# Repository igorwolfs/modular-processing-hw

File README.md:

# MCU-BOARD

## Acoustic-carrier Project
The goal is to design a small CPU board, with some RAM and connectors, that can
- Drive the piezo-driver / inverter board
- Save about 1 second of data from 2 30 MHz ADC's
	- Reflection at origin-piezo
	- Transmission from origin to second-piezo
- Processing of the data on the MCU in the next few seconds
- Storage of the processed data on an SD-CARD
- Transmission of the processed data over Hi-Speed USB / Ethernet to a computer

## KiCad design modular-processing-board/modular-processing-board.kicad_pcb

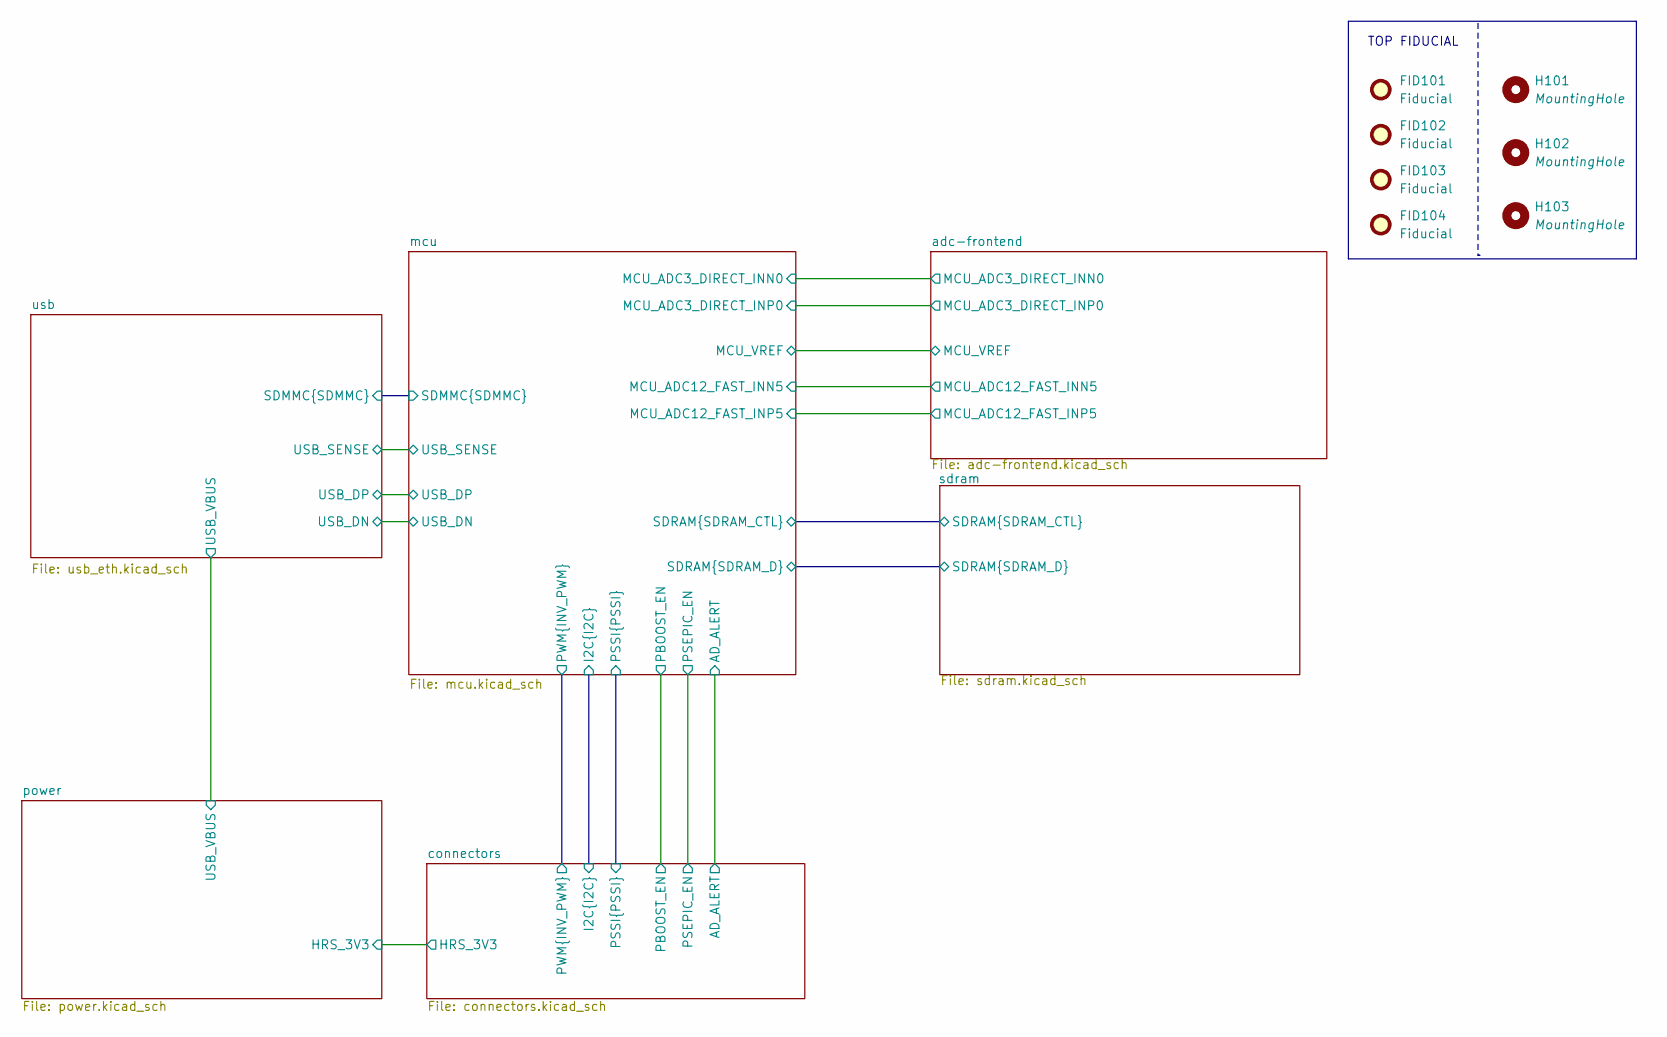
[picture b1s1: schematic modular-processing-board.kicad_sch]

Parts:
FID101, FID102, FID103, FID104: Fiducial; Fiducial_1mm_Mask2mm
H101, H102, H103: MountingHole; ToolingHole_1.152mm

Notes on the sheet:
TOP FIDUCIAL

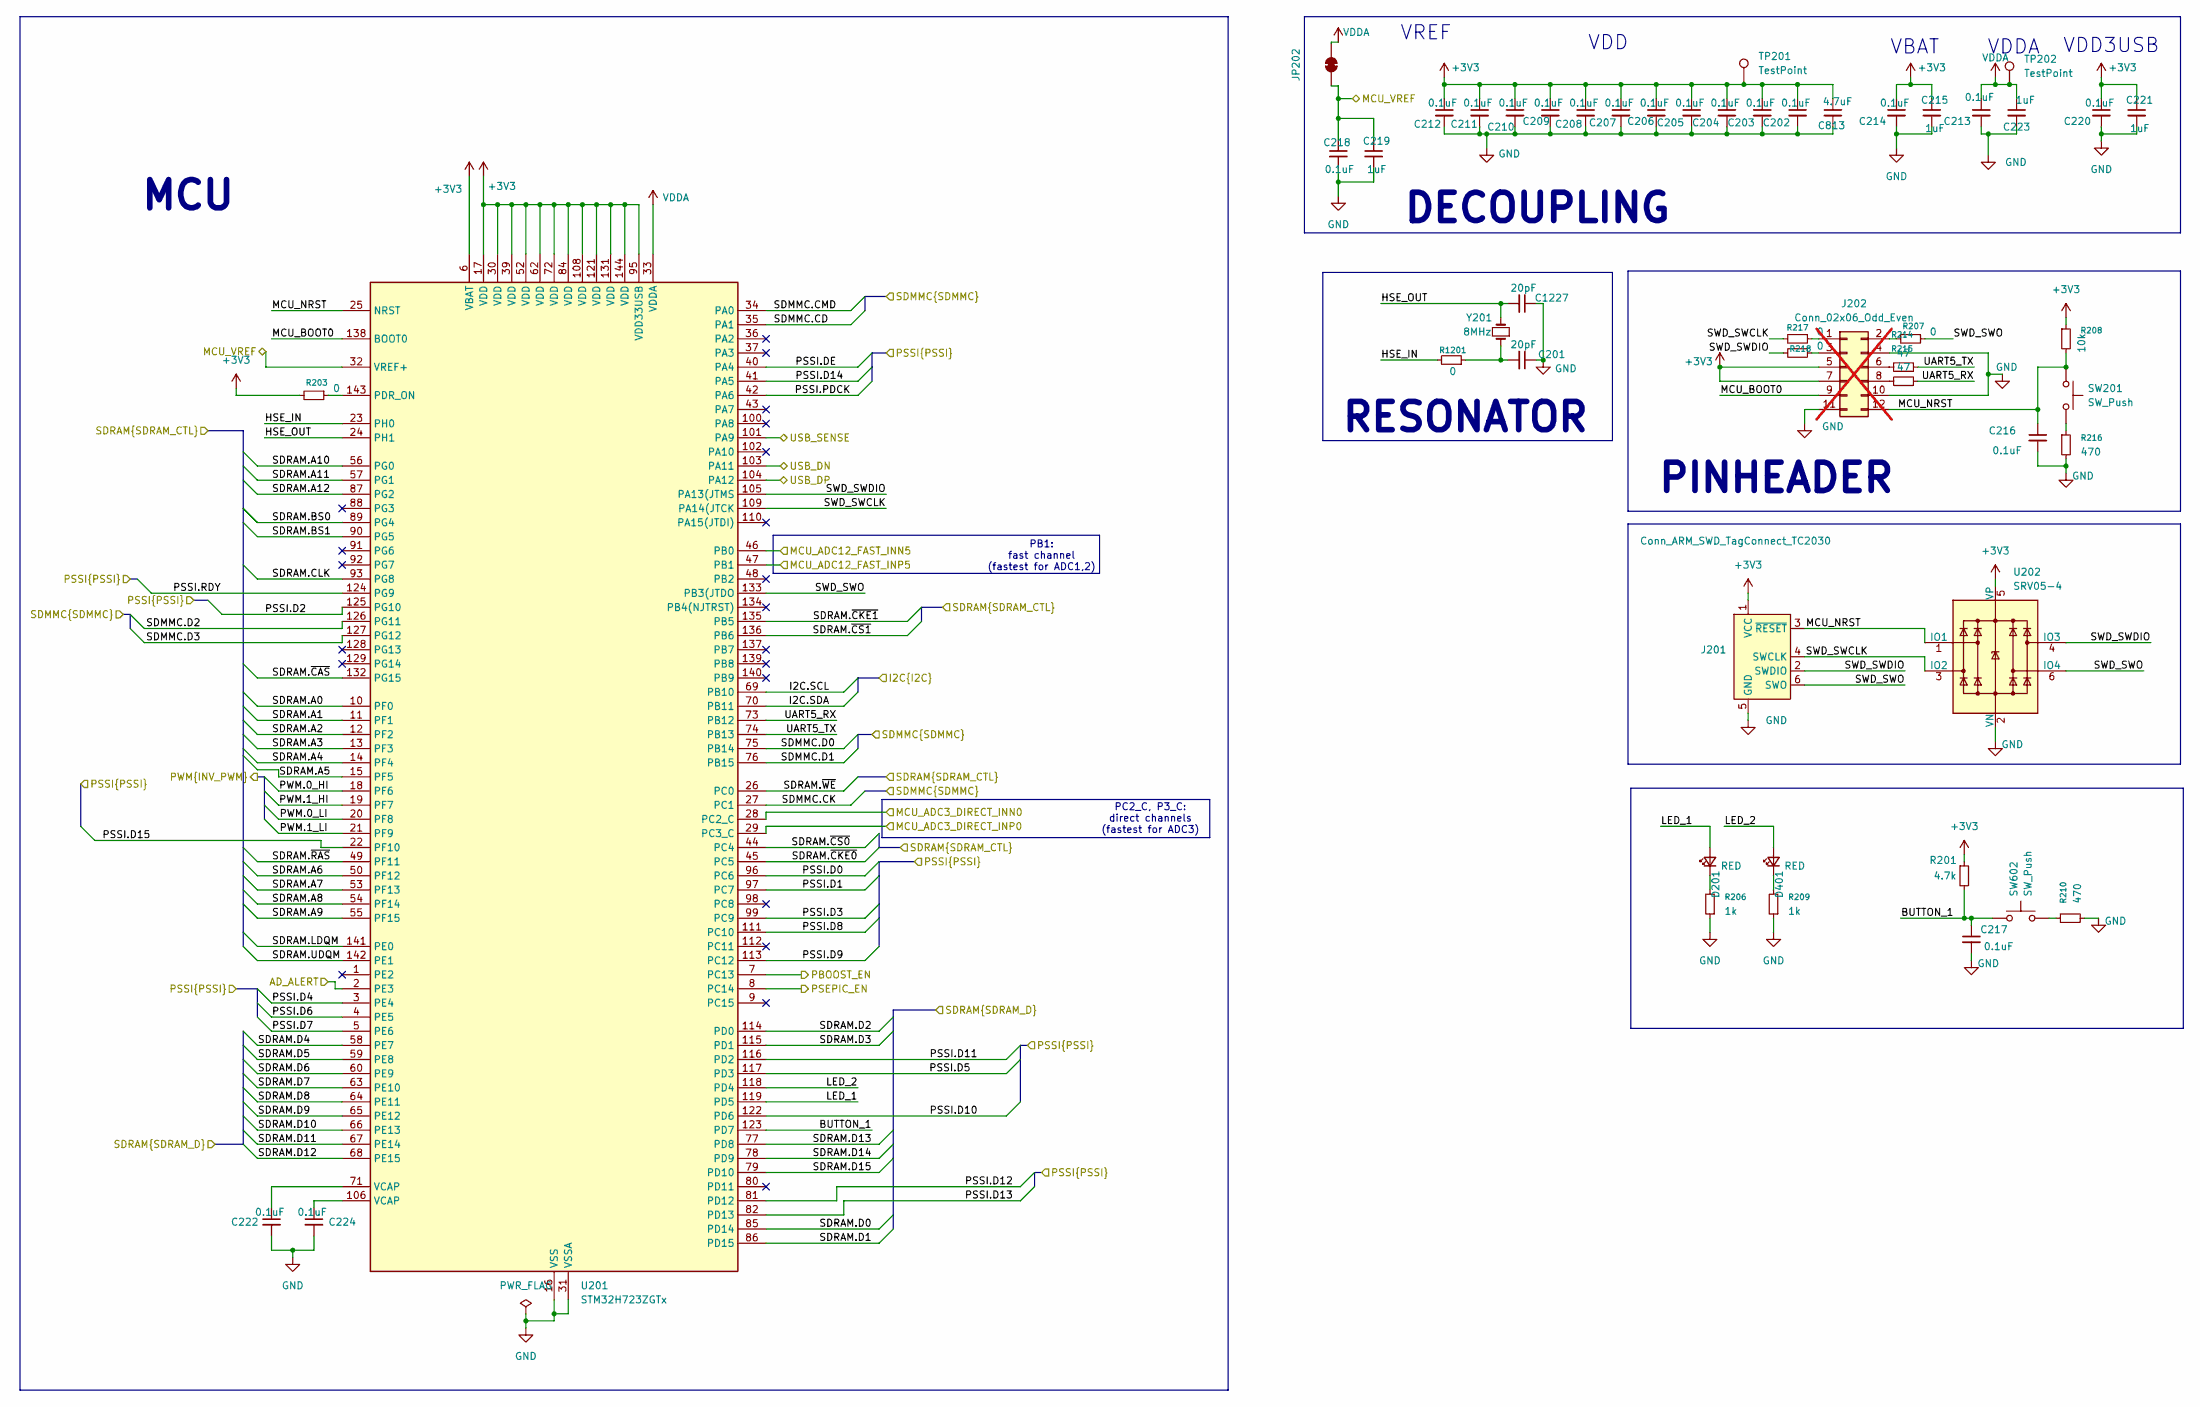
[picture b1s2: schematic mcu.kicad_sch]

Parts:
C201, C1227: 20pF; C_0402_1005Metric; MPN 0402CG200J500NT
C202, C203, C204, C205, C206, C207, C208, C209, C210, C211, C212, C213, C214, C216, C217, C218, C220, C222, C224: 0.1uF; C_0402_1005Metric; MPN CL05B104KB54PNC
C215, C219, C221, C223: 1uF; C_0805_2012Metric; MPN CL21B105KBFNNNE
C813: 4.7uF; C_0402_1005Metric; MPN CL05A475MP5NRNC
D201, D401: RED; LED_0603_1608Metric; MPN KT-0603R
J201: Conn_ARM_SWD_TagConnect_TC2030; Tag-Connect_TC2030-IDC-FP_2x03_P1.27mm_Vertical
J202: Conn_02x06_Odd_Even; PinHeader_2x06_P2.54mm_Vertical; not fitted
JP202: SolderJumper_2_Bridged; SolderJumper-2_P1.3mm_Bridged2Bar_Pad1.0x1.5mm
R201: 4.7k; R_0402_1005Metric; MPN 0402WGF4701TCE
R203, R207, R217, R218, R1201: 0; R_0603_1608Metric; MPN 0603WAF0000T5E
R206, R209: 1k; R_0402_1005Metric; MPN 0402WGF1001TCE
R208: 10k; R_0603_1608Metric; MPN 0603WAF1002T5E
R210, R216: 470; R_0402_1005Metric; MPN 0402WGF4700TCE
R214, R215: 47; R_0603_1608Metric; MPN 0603WAF470JT5E
SW201, SW602: SW_Push; SW_TS-1088-AR02016; MPN TS-1088-AR02016
TP201, TP202: TestPoint; PinSocket_1x01_P1.27mm_Vertical
U201: STM32H723ZGTx; LQFP-144_20x20mm_P0.5mm; MPN STM32H723ZGT6
U202: SRV05-4; SOT-23-6; MPN SRV05-4A
Y201: 8MHz; Crystal_SMD_5032-2Pin_5.0x3.2mm; MPN X50328MSB2GI

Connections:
+3V3: C202.1, C203.1, C204.1, C205.1, C206.1, C207.1, C208.1, C209.1, C210.1, C211.1, C212.1, C214.1, C215.1, C220.1, C221.1, C813.1, J201.1 (VCC), J202.5, J202.7, R201.1, R203.2, R208.1, TP201.1, U201.6 (VBAT), U201.17 (VDD), U201.30 (VDD), U201.39 (VDD), U201.52 (VDD), U201.62 (VDD), U201.72 (VDD), U201.84 (VDD), U201.95 (VDD33USB), U201.108 (VDD), U201.121 (VDD), U201.131 (VDD), U201.144 (VDD), U202.5 (VP); also elsewhere on the board
/adc-frontend/MCU_ADC3_DIRECT_INN0: U201.28 (PC2_C); also elsewhere on the board
/adc-frontend/MCU_ADC3_DIRECT_INP0: U201.29 (PC3_C); also elsewhere on the board
/adc-frontend/MCU_ADC12_FAST_INN5: U201.46 (PB0); also elsewhere on the board
/adc-frontend/MCU_ADC12_FAST_INP5: U201.47 (PB1); also elsewhere on the board
/adc-frontend/MCU_VREF: C218.1, C219.1, JP202.1 (A), U201.32 (VREF+); also elsewhere on the board
/connectors/AD_ALERT: U201.2 (PE3); also elsewhere on the board
/connectors/I2C.SCL: U201.69 (PB10); also elsewhere on the board
/connectors/I2C.SDA: U201.70 (PB11); also elsewhere on the board
/connectors/PBOOST_EN: U201.7 (PC13); also elsewhere on the board
/connectors/PSEPIC_EN: U201.8 (PC14); also elsewhere on the board
/connectors/PSSI.D0: U201.96 (PC6); also elsewhere on the board
/connectors/PSSI.D1: U201.97 (PC7); also elsewhere on the board
/connectors/PSSI.D2: U201.125 (PG10); also elsewhere on the board
/connectors/PSSI.D3: U201.99 (PC9); also elsewhere on the board
/connectors/PSSI.D4: U201.3 (PE4); also elsewhere on the board
/connectors/PSSI.D5: U201.117 (PD3); also elsewhere on the board
/connectors/PSSI.D6: U201.4 (PE5); also elsewhere on the board
/connectors/PSSI.D7: U201.5 (PE6); also elsewhere on the board
/connectors/PSSI.D8: U201.111 (PC10); also elsewhere on the board
/connectors/PSSI.D9: U201.113 (PC12); also elsewhere on the board
/connectors/PSSI.D10: U201.122 (PD6); also elsewhere on the board
/connectors/PSSI.D11: U201.116 (PD2); also elsewhere on the board
/connectors/PSSI.D12: U201.81 (PD12); also elsewhere on the board
/connectors/PSSI.D13: U201.82 (PD13); also elsewhere on the board
/connectors/PSSI.D14: U201.41 (PA5); also elsewhere on the board
/connectors/PSSI.D15: U201.22 (PF10); also elsewhere on the board
/connectors/PSSI.DE: U201.40 (PA4); also elsewhere on the board
/connectors/PSSI.PDCK: U201.42 (PA6); also elsewhere on the board
/connectors/PSSI.RDY: U201.124 (PG9); also elsewhere on the board
/connectors/PWM.0_HI: U201.18 (PF6); also elsewhere on the board
/connectors/PWM.0_LI: U201.20 (PF8); also elsewhere on the board
/connectors/PWM.1_HI: U201.19 (PF7); also elsewhere on the board
/connectors/PWM.1_LI: U201.21 (PF9); also elsewhere on the board
/mcu/BUTTON_1: C217.1, R201.2, SW602.1, U201.123 (PD7)
/mcu/HSE_IN: R1201.2, U201.23 (PH0)
/mcu/HSE_OUT: C1227.2, U201.24 (PH1), Y201.2
/mcu/LED_1: D201.2 (A), U201.119 (PD5)
/mcu/LED_2: D401.2 (A), U201.118 (PD4)
/mcu/MCU_BOOT0: J202.9, U201.138 (BOOT0)
/mcu/MCU_NRST: C216.1, J201.3 (~RESET), J202.12, R208.2, SW201.1, U201.25 (NRST), U202.1 (IO1)
/mcu/SDMMC.CD: U201.35 (PA1); also elsewhere on the board
/mcu/SDMMC.CK: U201.27 (PC1); also elsewhere on the board
/mcu/SDMMC.CMD: U201.34 (PA0); also elsewhere on the board
/mcu/SDMMC.D0: U201.75 (PB14); also elsewhere on the board
/mcu/SDMMC.D1: U201.76 (PB15); also elsewhere on the board
/mcu/SDMMC.D2: U201.126 (PG11); also elsewhere on the board
/mcu/SDMMC.D3: U201.127 (PG12); also elsewhere on the board
/mcu/SDRAM.A0: U201.10 (PF0); also elsewhere on the board
/mcu/SDRAM.A1: U201.11 (PF1); also elsewhere on the board
/mcu/SDRAM.A2: U201.12 (PF2); also elsewhere on the board
/mcu/SDRAM.A3: U201.13 (PF3); also elsewhere on the board
/mcu/SDRAM.A4: U201.14 (PF4); also elsewhere on the board
/mcu/SDRAM.A5: U201.15 (PF5); also elsewhere on the board
/mcu/SDRAM.A6: U201.50 (PF12); also elsewhere on the board
/mcu/SDRAM.A7: U201.53 (PF13); also elsewhere on the board
/mcu/SDRAM.A8: U201.54 (PF14); also elsewhere on the board
/mcu/SDRAM.A9: U201.55 (PF15); also elsewhere on the board
/mcu/SDRAM.A10: U201.56 (PG0); also elsewhere on the board
/mcu/SDRAM.A11: U201.57 (PG1); also elsewhere on the board
/mcu/SDRAM.A12: U201.87 (PG2); also elsewhere on the board
/mcu/SDRAM.BS0: U201.89 (PG4); also elsewhere on the board
/mcu/SDRAM.BS1: U201.90 (PG5); also elsewhere on the board
/mcu/SDRAM.CLK: U201.93 (PG8); also elsewhere on the board
/mcu/SDRAM.D0: U201.85 (PD14); also elsewhere on the board
/mcu/SDRAM.D1: U201.86 (PD15); also elsewhere on the board
/mcu/SDRAM.D2: U201.114 (PD0); also elsewhere on the board
/mcu/SDRAM.D3: U201.115 (PD1); also elsewhere on the board
/mcu/SDRAM.D4: U201.58 (PE7); also elsewhere on the board
/mcu/SDRAM.D5: U201.59 (PE8); also elsewhere on the board
/mcu/SDRAM.D6: U201.60 (PE9); also elsewhere on the board
/mcu/SDRAM.D7: U201.63 (PE10); also elsewhere on the board
/mcu/SDRAM.D8: U201.64 (PE11); also elsewhere on the board
/mcu/SDRAM.D9: U201.65 (PE12); also elsewhere on the board
/mcu/SDRAM.D10: U201.66 (PE13); also elsewhere on the board
/mcu/SDRAM.D11: U201.67 (PE14); also elsewhere on the board
/mcu/SDRAM.D12: U201.68 (PE15); also elsewhere on the board
/mcu/SDRAM.D13: U201.77 (PD8); also elsewhere on the board
/mcu/SDRAM.D14: U201.78 (PD9); also elsewhere on the board
/mcu/SDRAM.D15: U201.79 (PD10); also elsewhere on the board
/mcu/SDRAM.LDQM: U201.141 (PE0); also elsewhere on the board
/mcu/SDRAM.UDQM: U201.142 (PE1); also elsewhere on the board
/mcu/SDRAM.~CAS: U201.132 (PG15); also elsewhere on the board
/mcu/SDRAM.~CKE0: U201.45 (PC5); also elsewhere on the board
/mcu/SDRAM.~CKE1: U201.135 (PB5); also elsewhere on the board
/mcu/SDRAM.~CS0: U201.44 (PC4); also elsewhere on the board
/mcu/SDRAM.~CS1: U201.136 (PB6); also elsewhere on the board
/mcu/SDRAM.~RAS: U201.49 (PF11); also elsewhere on the board
/mcu/SDRAM.~WE: U201.26 (PC0); also elsewhere on the board
/mcu/SWD_SWCLK: J201.4 (SWCLK), R217.2, U201.109 (PA14(JTCK), U202.3 (IO2)
/mcu/SWD_SWDIO: J201.2 (SWDIO), R218.2, U201.105 (PA13(JTMS), U202.4 (IO3)
/mcu/SWD_SWO: J201.6 (SWO), R207.1, U201.133 (PB3(JTDO), U202.6 (IO4)
/mcu/UART5_RX: R215.1, U201.73 (PB12)
/mcu/UART5_TX: R214.1, U201.74 (PB13)
/mcu/USB_DN: U201.103 (PA11); also elsewhere on the board
/mcu/USB_DP: U201.104 (PA12); also elsewhere on the board
/mcu/USB_SENSE: U201.101 (PA9); also elsewhere on the board
GND: C201.1, C202.2, C203.2, C204.2, C205.2, C206.2, C207.2, C208.2, C209.2, C210.2, C211.2, C212.2, C213.2, C214.2, C215.2, C216.2, C217.2, C218.2, C219.2, C220.2, C221.2, C222.2, C223.2, C224.2, C813.2, C1227.1, J201.5 (GND), J202.4, J202.10, J202.11, R206.1, R209.1, R210.2, R216.2, U201.16 (VSS), U201.31 (VSSA), U201.38 (VSS), U201.51 (VSS), U201.61 (VSS), U201.83 (VSS), U201.94 (VSS), U201.107 (VSS), U201.120 (VSS), U201.130 (VSS), U202.2 (VN); also elsewhere on the board
unnamed: C201.2, R1201.1, Y201.1
unnamed: C222.1, U201.71 (VCAP)
unnamed: C224.1, U201.106 (VCAP)
unnamed: D201.1 (K), R206.2
unnamed: D401.1 (K), R209.2
unnamed: J202.1, R217.1
unnamed: J202.2, R207.2
unnamed: J202.3, R218.1
unnamed: J202.6, R214.2
unnamed: J202.8, R215.2
unnamed: R210.1, SW602.2
unnamed: R216.1, SW201.2
unnamed: R203.1, U201.143 (PDR_ON)
VDDA: C213.1, C223.1, JP202.2 (B), TP202.1, U201.33 (VDDA); also elsewhere on the board

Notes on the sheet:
PINHEADER
PB1: fast channel (fastest for ADC1,2)
MCU
PC2_C, P3_C: direct channels (fastest for ADC3)
VDD3USB
VDD
RESONATOR
VREF
DECOUPLING
VBAT
VDDA

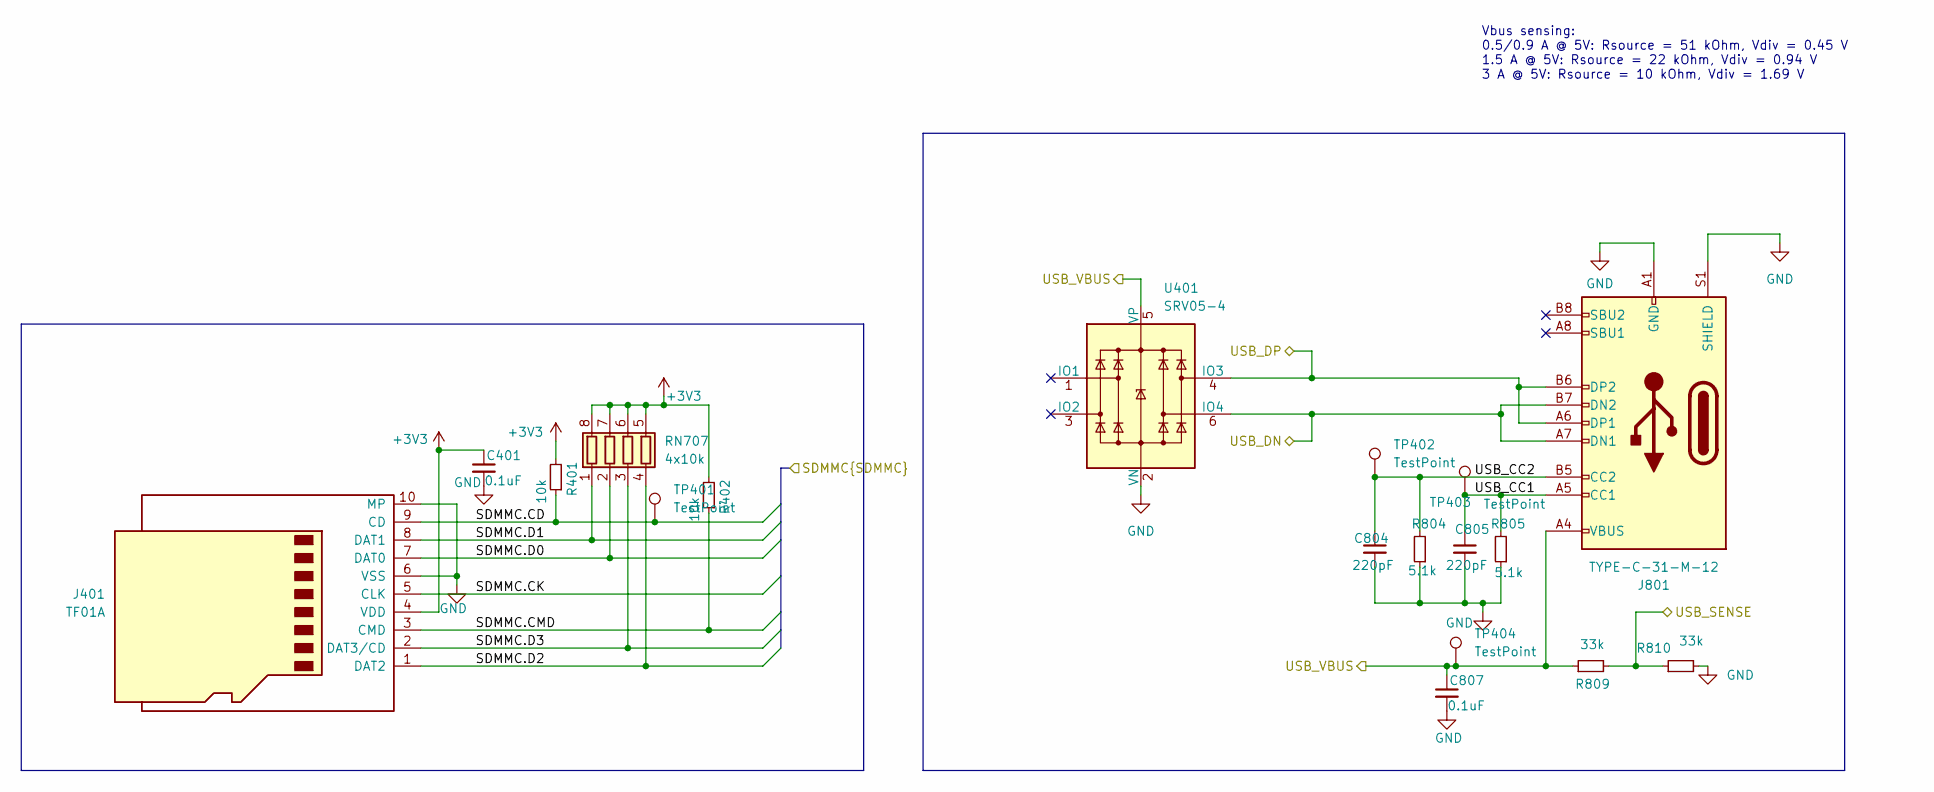
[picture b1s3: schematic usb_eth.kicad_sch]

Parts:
C401, C807: 0.1uF; C_0402_1005Metric; MPN CL05B104KB54PNC
C804, C805: 220pF; C_0402_1005Metric; MPN 0402B221K500NT
J401: TF01A; MPN TF-01A
J801: TYPE-C-31-M-12; USB_C_Receptacle_HRO_TYPE-C-31-M-12; MPN TYPE-C-31-M-12
R401, R402: 10k; R_0603_1608Metric; MPN 0603WAF1002T5E
R804, R805: 5.1k; R_0603_1608Metric; MPN 0603WAF5101T5E
R809, R810: 33k; R_0603_1608Metric; MPN 0603WAF3302T5E
RN707: 4x10k; R_Array_Convex_4x0603; MPN 4D03WGJ0103T5E
TP401, TP402, TP403, TP404: TestPoint; PinSocket_1x01_P1.27mm_Vertical
U401: SRV05-4; SOT-23-6; MPN SRV05-4A

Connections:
+3V3: C401.1, J401.4 (VDD), R401.2, R402.2, RN707.5 (R4.2), RN707.6 (R3.2), RN707.7 (R2.2), RN707.8 (R1.2); also elsewhere on the board
/mcu/SDMMC.CD: J401.9 (CD), R401.1, TP401.1; also elsewhere on the board
/mcu/SDMMC.CK: J401.5 (CLK); also elsewhere on the board
/mcu/SDMMC.CMD: J401.3 (CMD), R402.1; also elsewhere on the board
/mcu/SDMMC.D0: J401.7 (DAT0), RN707.2 (R2.1); also elsewhere on the board
/mcu/SDMMC.D1: J401.8 (DAT1), RN707.1 (R1.1); also elsewhere on the board
/mcu/SDMMC.D2: J401.1 (DAT2), RN707.4 (R4.1); also elsewhere on the board
/mcu/SDMMC.D3: J401.2 (DAT3/CD), RN707.3 (R3.1); also elsewhere on the board
/mcu/USB_DN: J801.A7 (DN1), J801.B7 (DN2), U401.6 (IO4); also elsewhere on the board
/mcu/USB_DP: J801.A6 (DP1), J801.B6 (DP2), U401.4 (IO3); also elsewhere on the board
/mcu/USB_SENSE: R809.2, R810.1; also elsewhere on the board
/power/USB_VBUS: C807.1, J801.A4 (VBUS), J801.A9 (VBUS), J801.B4 (VBUS), J801.B9 (VBUS), R809.1, TP404.1, U401.5 (VP); also elsewhere on the board
/usb/USB_CC1: C805.1, J801.A5 (CC1), R805.2, TP403.1
/usb/USB_CC2: C804.1, J801.B5 (CC2), R804.2, TP402.1
GND: C401.2, C804.2, C805.2, C807.2, J401.6 (VSS), J401.10 (MP), J801.A1 (GND), J801.A12 (GND), J801.B1 (GND), J801.B12 (GND), J801.S1 (SHIELD), R804.1, R805.1, R810.2, U401.2 (VN); also elsewhere on the board

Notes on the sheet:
Vbus sensing: 0.5/0.9 A @ 5V: Rsource = 51 kOhm, Vdiv = 0.45 V 1.5 A @ 5V: Rsource = 22 kOhm, Vdiv = 0.94 V 3 A @ 5V: Rsource = 10 kOhm, Vdiv = 1.69 V

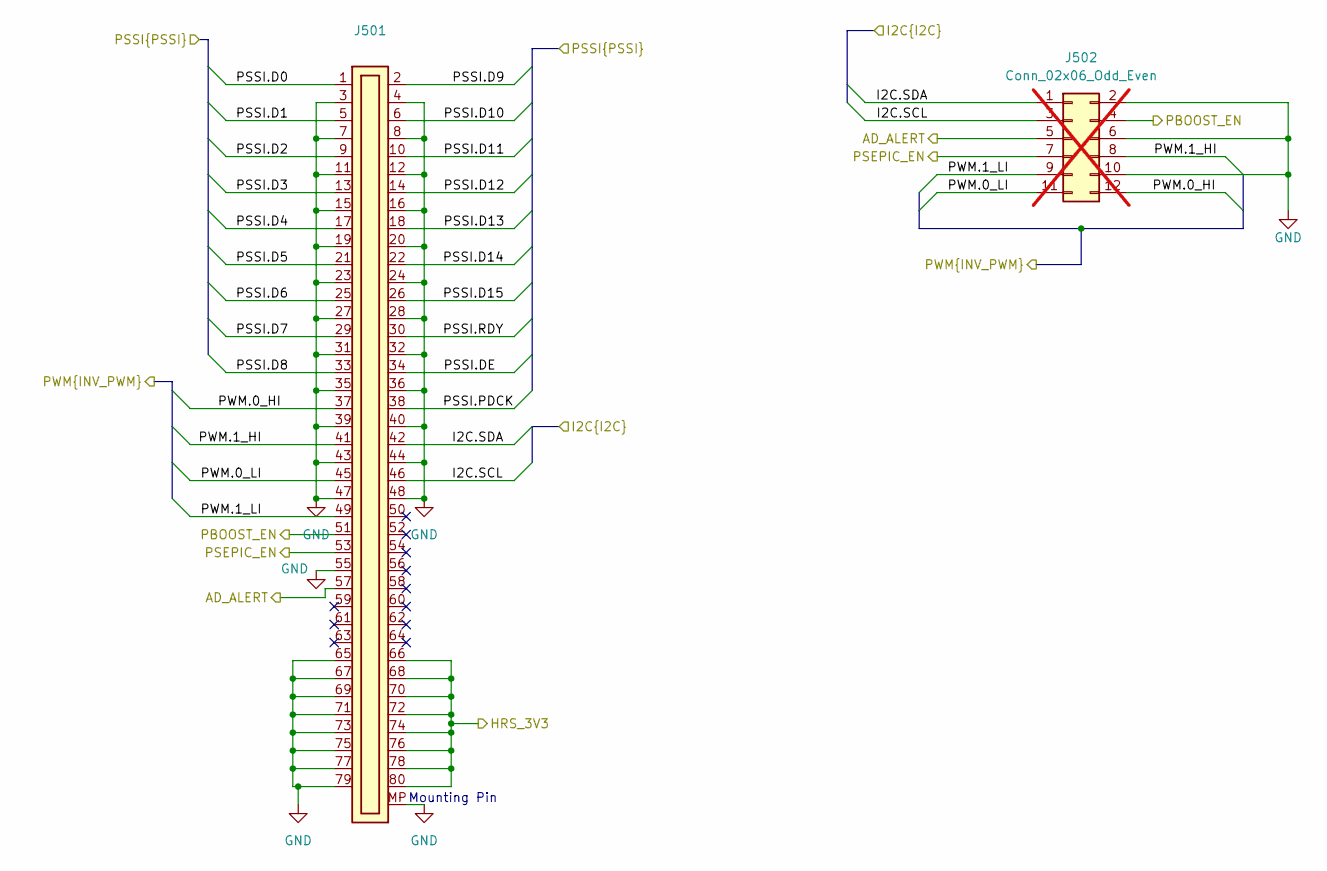
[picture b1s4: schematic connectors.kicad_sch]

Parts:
J501: Plug_Hirose_DF40_2x40_DF40C-80DP-0.4V; HRS_DF40C-80DP-0.4V(51); MPN DF40C-80DP-0.4V(51)
J502: Conn_02x06_Odd_Even; PinSocket_2x06_P2.54mm_Vertical; not fitted

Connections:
/connectors/AD_ALERT: J501.57, J502.5; also elsewhere on the board
/connectors/HRS_3V3: J501.66, J501.68, J501.70, J501.72, J501.74, J501.76, J501.78, J501.80; also elsewhere on the board
/connectors/I2C.SCL: J501.46, J502.3; also elsewhere on the board
/connectors/I2C.SDA: J501.42, J502.1; also elsewhere on the board
/connectors/PBOOST_EN: J501.51, J502.4; also elsewhere on the board
/connectors/PSEPIC_EN: J501.53, J502.7; also elsewhere on the board
/connectors/PSSI.D0: J501.1; also elsewhere on the board
/connectors/PSSI.D1: J501.5; also elsewhere on the board
/connectors/PSSI.D2: J501.9; also elsewhere on the board
/connectors/PSSI.D3: J501.13; also elsewhere on the board
/connectors/PSSI.D4: J501.17; also elsewhere on the board
/connectors/PSSI.D5: J501.21; also elsewhere on the board
/connectors/PSSI.D6: J501.25; also elsewhere on the board
/connectors/PSSI.D7: J501.29; also elsewhere on the board
/connectors/PSSI.D8: J501.33; also elsewhere on the board
/connectors/PSSI.D9: J501.2; also elsewhere on the board
/connectors/PSSI.D10: J501.6; also elsewhere on the board
/connectors/PSSI.D11: J501.10; also elsewhere on the board
/connectors/PSSI.D12: J501.14; also elsewhere on the board
/connectors/PSSI.D13: J501.18; also elsewhere on the board
/connectors/PSSI.D14: J501.22; also elsewhere on the board
/connectors/PSSI.D15: J501.26; also elsewhere on the board
/connectors/PSSI.DE: J501.34; also elsewhere on the board
/connectors/PSSI.PDCK: J501.38; also elsewhere on the board
/connectors/PSSI.RDY: J501.30; also elsewhere on the board
/connectors/PWM.0_HI: J501.37, J502.12; also elsewhere on the board
/connectors/PWM.0_LI: J501.45, J502.11; also elsewhere on the board
/connectors/PWM.1_HI: J501.41, J502.8; also elsewhere on the board
/connectors/PWM.1_LI: J501.49, J502.9; also elsewhere on the board
GND: J501.3, J501.4, J501.7, J501.8, J501.11, J501.12, J501.15, J501.16, J501.19, J501.20, J501.23, J501.24, J501.27, J501.28, J501.31, J501.32, J501.35, J501.36, J501.39, J501.40, J501.43, J501.44, J501.47, J501.48, J501.55, J501.65, J501.67, J501.69, J501.71, J501.73, J501.75, J501.77, J501.79, J501.MP, J502.2, J502.6, J502.10; also elsewhere on the board

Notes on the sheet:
Mounting Pin

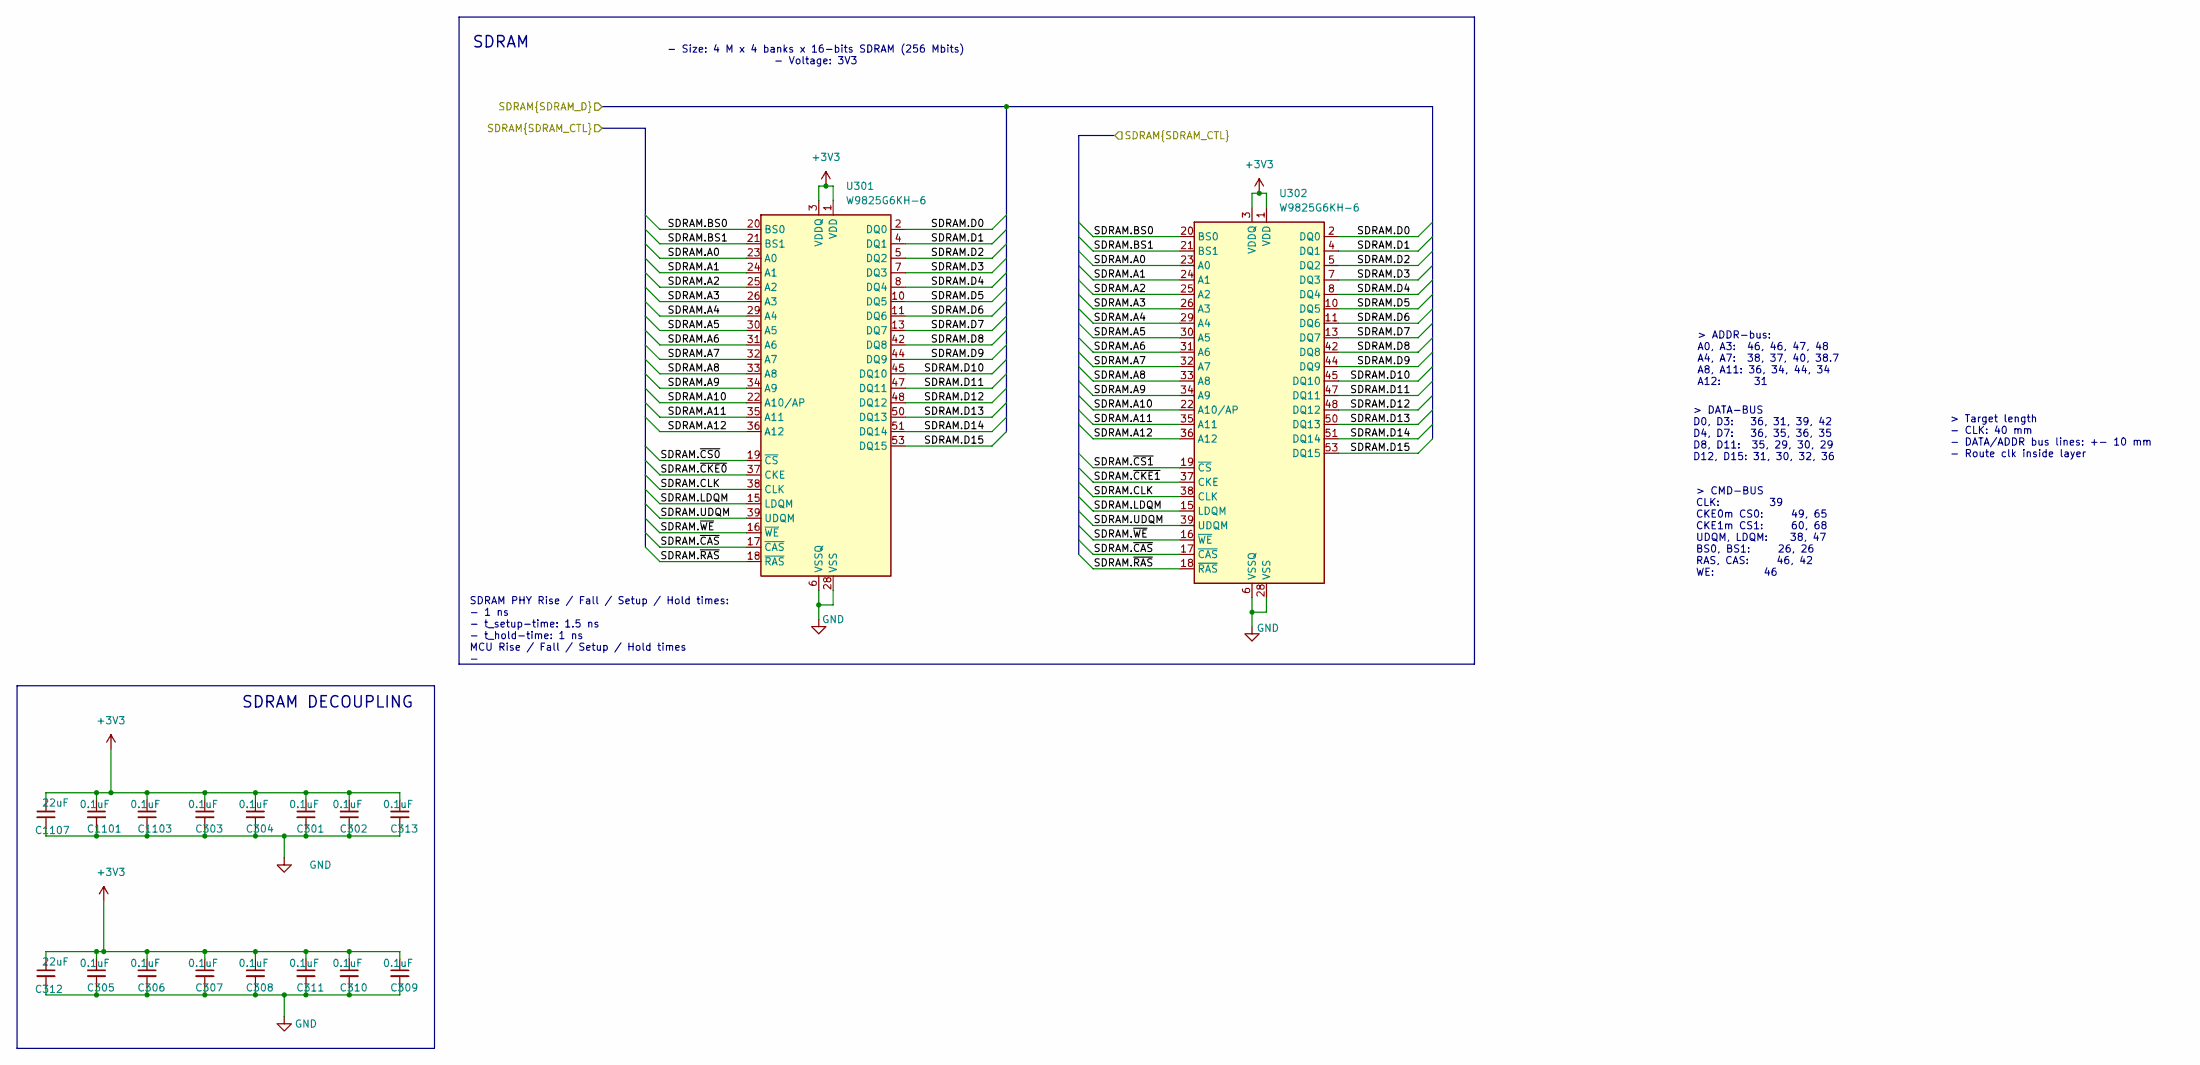
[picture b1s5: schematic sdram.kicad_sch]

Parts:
C301, C302, C303, C304, C305, C306, C307, C308, C309, C310, C311, C313, C1101, C1103: 0.1uF; C_0402_1005Metric; MPN CL05B104KB54PNC
C312, C1107: 22uF; C_0603_1608Metric; MPN CL10A226MQ8NRNC
U301, U302: W9825G6KH-6; TSOP-II-54_22.2x10.16mm_P0.8mm; MPN W9825G6KH-6

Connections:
+3V3: C301.1, C302.1, C303.1, C304.1, C305.1, C306.1, C307.1, C308.1, C309.1, C310.1, C311.1, C312.1, C313.1, C1101.1, C1103.1, C1107.1, U301.1 (VDD), U301.3 (VDDQ), U301.9 (VDDQ), U301.14 (VDD), U301.27 (VDD), U301.43 (VDDQ), U301.49 (VDDQ), U302.1 (VDD), U302.3 (VDDQ), U302.9 (VDDQ), U302.14 (VDD), U302.27 (VDD), U302.43 (VDDQ), U302.49 (VDDQ); also elsewhere on the board
/mcu/SDRAM.A0: U301.23 (A0), U302.23 (A0); also elsewhere on the board
/mcu/SDRAM.A1: U301.24 (A1), U302.24 (A1); also elsewhere on the board
/mcu/SDRAM.A2: U301.25 (A2), U302.25 (A2); also elsewhere on the board
/mcu/SDRAM.A3: U301.26 (A3), U302.26 (A3); also elsewhere on the board
/mcu/SDRAM.A4: U301.29 (A4), U302.29 (A4); also elsewhere on the board
/mcu/SDRAM.A5: U301.30 (A5), U302.30 (A5); also elsewhere on the board
/mcu/SDRAM.A6: U301.31 (A6), U302.31 (A6); also elsewhere on the board
/mcu/SDRAM.A7: U301.32 (A7), U302.32 (A7); also elsewhere on the board
/mcu/SDRAM.A8: U301.33 (A8), U302.33 (A8); also elsewhere on the board
/mcu/SDRAM.A9: U301.34 (A9), U302.34 (A9); also elsewhere on the board
/mcu/SDRAM.A10: U301.22 (A10/AP), U302.22 (A10/AP); also elsewhere on the board
/mcu/SDRAM.A11: U301.35 (A11), U302.35 (A11); also elsewhere on the board
/mcu/SDRAM.A12: U301.36 (A12), U302.36 (A12); also elsewhere on the board
/mcu/SDRAM.BS0: U301.20 (BS0), U302.20 (BS0); also elsewhere on the board
/mcu/SDRAM.BS1: U301.21 (BS1), U302.21 (BS1); also elsewhere on the board
/mcu/SDRAM.CLK: U301.38 (CLK), U302.38 (CLK); also elsewhere on the board
/mcu/SDRAM.D0: U301.2 (DQ0), U302.2 (DQ0); also elsewhere on the board
/mcu/SDRAM.D1: U301.4 (DQ1), U302.4 (DQ1); also elsewhere on the board
/mcu/SDRAM.D2: U301.5 (DQ2), U302.5 (DQ2); also elsewhere on the board
/mcu/SDRAM.D3: U301.7 (DQ3), U302.7 (DQ3); also elsewhere on the board
/mcu/SDRAM.D4: U301.8 (DQ4), U302.8 (DQ4); also elsewhere on the board
/mcu/SDRAM.D5: U301.10 (DQ5), U302.10 (DQ5); also elsewhere on the board
/mcu/SDRAM.D6: U301.11 (DQ6), U302.11 (DQ6); also elsewhere on the board
/mcu/SDRAM.D7: U301.13 (DQ7), U302.13 (DQ7); also elsewhere on the board
/mcu/SDRAM.D8: U301.42 (DQ8), U302.42 (DQ8); also elsewhere on the board
/mcu/SDRAM.D9: U301.44 (DQ9), U302.44 (DQ9); also elsewhere on the board
/mcu/SDRAM.D10: U301.45 (DQ10), U302.45 (DQ10); also elsewhere on the board
/mcu/SDRAM.D11: U301.47 (DQ11), U302.47 (DQ11); also elsewhere on the board
/mcu/SDRAM.D12: U301.48 (DQ12), U302.48 (DQ12); also elsewhere on the board
/mcu/SDRAM.D13: U301.50 (DQ13), U302.50 (DQ13); also elsewhere on the board
/mcu/SDRAM.D14: U301.51 (DQ14), U302.51 (DQ14); also elsewhere on the board
/mcu/SDRAM.D15: U301.53 (DQ15), U302.53 (DQ15); also elsewhere on the board
/mcu/SDRAM.LDQM: U301.15 (LDQM), U302.15 (LDQM); also elsewhere on the board
/mcu/SDRAM.UDQM: U301.39 (UDQM), U302.39 (UDQM); also elsewhere on the board
/mcu/SDRAM.~CAS: U301.17 (~CAS), U302.17 (~CAS); also elsewhere on the board
/mcu/SDRAM.~CKE0: U301.37 (CKE); also elsewhere on the board
/mcu/SDRAM.~CKE1: U302.37 (CKE); also elsewhere on the board
/mcu/SDRAM.~CS0: U301.19 (~CS); also elsewhere on the board
/mcu/SDRAM.~CS1: U302.19 (~CS); also elsewhere on the board
/mcu/SDRAM.~RAS: U301.18 (~RAS), U302.18 (~RAS); also elsewhere on the board
/mcu/SDRAM.~WE: U301.16 (~WE), U302.16 (~WE); also elsewhere on the board
GND: C301.2, C302.2, C303.2, C304.2, C305.2, C306.2, C307.2, C308.2, C309.2, C310.2, C311.2, C312.2, C313.2, C1101.2, C1103.2, C1107.2, U301.6 (VSSQ), U301.12 (VSSQ), U301.28 (VSS), U301.41 (VSS), U301.46 (VSSQ), U301.52 (VSSQ), U301.54 (VSS), U302.6 (VSSQ), U302.12 (VSSQ), U302.28 (VSS), U302.41 (VSS), U302.46 (VSSQ), U302.52 (VSSQ), U302.54 (VSS); also elsewhere on the board

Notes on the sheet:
> DATA-BUS D0, D3: 36, 31, 39, 42 D4, D7: 36, 35, 36, 35 D8, D11: 35, 29, 30, 29 D12, D15: 31, 30, 32, 36
> Target length - CLK: 40 mm - DATA/ADDR bus lines: +- 10 mm - Route clk inside layer
> CMD-BUS CLK: 39 CKE0m CS0: 49, 65 CKE1m CS1: 60, 68 UDQM, LDQM: 38, 47 BS0, BS1: 26, 26 RAS, CAS: 46, 42 WE: 46
SDRAM PHY Rise / Fall / Setup / Hold times: - 1 ns - t_setup-time: 1.5 ns - t_hold-time: 1 ns MCU Rise / Fall / Setup / Hold times -
SDRAM DECOUPLING
SDRAM
> ADDR-bus: A0, A3: 46, 46, 47, 48 A4, A7: 38, 37, 40, 38.7 A8, A11: 36, 34, 44, 34 A12: 31
- Size: 4 M x 4 banks x 16-bits SDRAM (256 Mbits) - Voltage: 3V3

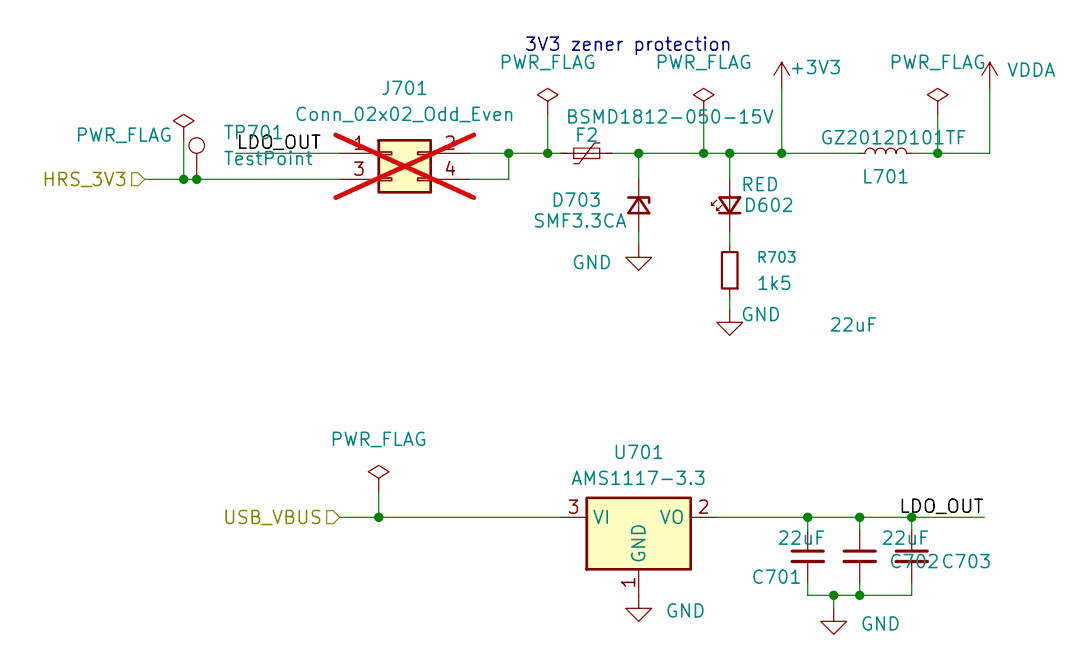
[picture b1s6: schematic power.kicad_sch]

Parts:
C701, C702, C703: 22uF; C_0603_1608Metric; MPN CL10A226MQ8NRNC
D602: RED; LED_0603_1608Metric; MPN KT-0603R
D703: SMF3.3CA; D_SOD-123F; MPN SMF3.3CA
F2: BSMD1812-050-15V; Fuse_1812_4532Metric; MPN BSMD1812-050-15V
J701: Conn_02x02_Odd_Even; PinHeader_2x02_P2.54mm_Vertical; not fitted
L701: GZ2012D101TF; L_0805_2012Metric; MPN GZ2012D101TF
R703: 1k5; R_0402_1005Metric; MPN 0402WGF1501TCE
TP701: TestPoint; PinSocket_1x01_P1.27mm_Vertical
U701: AMS1117-3.3; SOT-223-3_TabPin2; MPN AMS1117-3.3

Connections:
+3V3: D602.2 (A), D703.1 (K), F2.2, L701.1; also elsewhere on the board
/connectors/HRS_3V3: J701.3, TP701.1; also elsewhere on the board
/power/LDO_OUT: C701.1, C702.1, C703.1, J701.1, U701.2 (VO)
/power/USB_VBUS: U701.3 (VI); also elsewhere on the board
GND: C701.2, C702.2, C703.2, D703.2 (A), R703.1, U701.1 (GND); also elsewhere on the board
unnamed: D602.1 (K), R703.2
unnamed: F2.1, J701.2, J701.4
VDDA: L701.2; also elsewhere on the board

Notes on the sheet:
3V3 zener protection

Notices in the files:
parts and their libraries:
License: Apache-2.0
